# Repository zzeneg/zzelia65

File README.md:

# zzelia65

65% keyboard with external ProMicro-compatible controller.

Design inspired by [Neo Zelia](https://geekhack.org/index.php?topic=62449.0)

**⚠️ Design-stage only, not even a working prototype.**

## Main features

- Swappable controller, aimed to be wireless with [nice!nano](https://nicekeyboards.com/nice-nano/)
- Portable
- No plate
- No RGB
- Soldered switches

## Project structure

- `keyboard-layout.json` Layout file that can be imported into [keyboard-layout-editor](http://www.keyboard-layout-editor.com)
- `matrix-layout.json` Wiring configuration to be imported into [Keyboard Firmware Builder](https://builder.mrkeebs.com)
- `kicad` - KiCad project
- `gerber` - gerber files

## Layout

Standard 65% ANSI with exploded design.

## Wiring

ProMicro has only 18 pins by default so wiring is a bit tricky as we need to stay in the limit. The most logical was to use 10 rows and 8 columns. Can be improved, probably.

## Similar/inspirational projects

- [Contra](https://github.com/ai03-2725/Contra)
- [KBIC65](https://github.com/b-karl/KBIC65)
- [horizon](https://github.com/skarrmann/horizon)

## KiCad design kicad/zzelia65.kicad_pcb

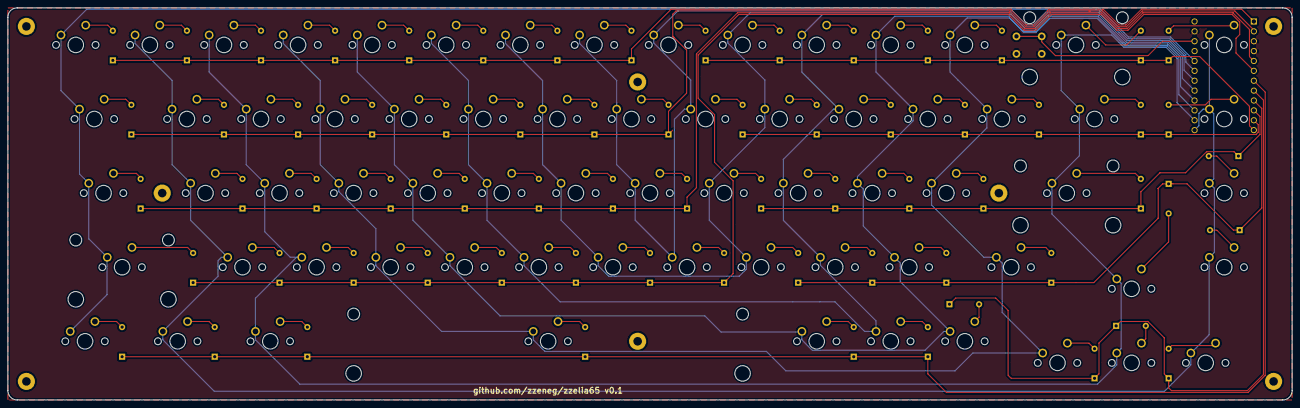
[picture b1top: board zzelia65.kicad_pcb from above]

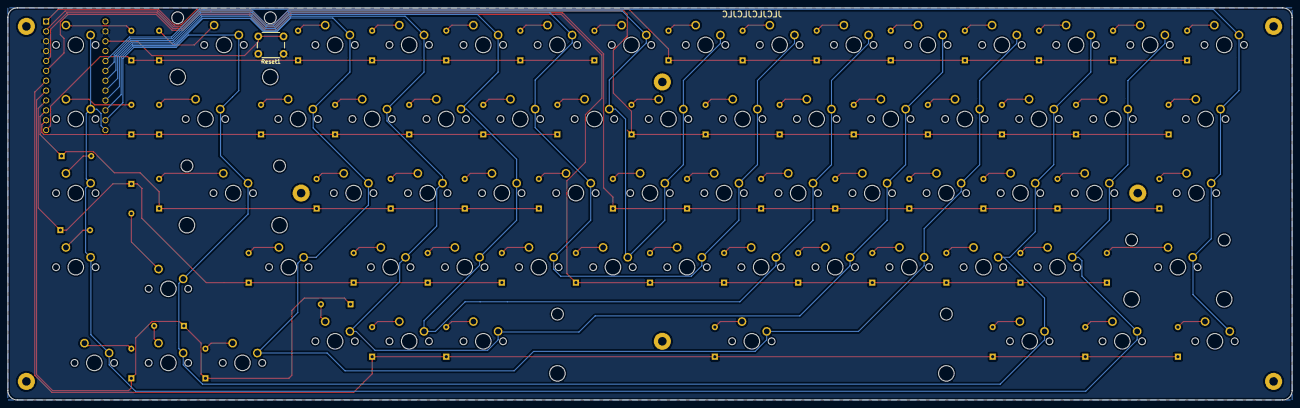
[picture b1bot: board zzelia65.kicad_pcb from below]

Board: 2 copper layers, 330.2 x 100.8 mm, 138 parts (2 on the bottom side), 10 nets.

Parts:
D_0, D_1, D_2, D_3, D_4, D_5, D_6, D_7, D_8, D_9: D_Small; D_DO-35_SOD27_P7.62mm_Horizontal
D_A1: D_Small; D_DO-35_SOD27_P7.62mm_Horizontal
D_B1: D_Small; D_DO-35_SOD27_P7.62mm_Horizontal
D_Back1: D_Small; D_DO-35_SOD27_P7.62mm_Horizontal
D_Backslash1: D_Small; D_DO-35_SOD27_P7.62mm_Horizontal
D_C1: D_Small; D_DO-35_SOD27_P7.62mm_Horizontal
D_Caps1: D_Small; D_DO-35_SOD27_P7.62mm_Horizontal
D_Close1: D_Small; D_DO-35_SOD27_P7.62mm_Horizontal
D_Comma1: D_Small; D_DO-35_SOD27_P7.62mm_Horizontal
D_D1: D_Small; D_DO-35_SOD27_P7.62mm_Horizontal
D_Del1: D_Small; D_DO-35_SOD27_P7.62mm_Horizontal
D_Dot1: D_Small; D_DO-35_SOD27_P7.62mm_Horizontal
D_Down1: D_Small; D_DO-35_SOD27_P7.62mm_Horizontal
D_E1: D_Small; D_DO-35_SOD27_P7.62mm_Horizontal
D_End1: D_Small; D_DO-35_SOD27_P7.62mm_Horizontal
D_Enter1: D_Small; D_DO-35_SOD27_P7.62mm_Horizontal
D_Esc1: D_Small; D_DO-35_SOD27_P7.62mm_Horizontal
D_F1: D_Small; D_DO-35_SOD27_P7.62mm_Horizontal
D_Fn1: D_Small; D_DO-35_SOD27_P7.62mm_Horizontal
D_G1: D_Small; D_DO-35_SOD27_P7.62mm_Horizontal
D_H1: D_Small; D_DO-35_SOD27_P7.62mm_Horizontal
D_Home1: D_Small; D_DO-35_SOD27_P7.62mm_Horizontal
D_I1: D_Small; D_DO-35_SOD27_P7.62mm_Horizontal
D_Insert1: D_Small; D_DO-35_SOD27_P7.62mm_Horizontal
D_J1: D_Small; D_DO-35_SOD27_P7.62mm_Horizontal
D_K1: D_Small; D_DO-35_SOD27_P7.62mm_Horizontal
D_L1: D_Small; D_DO-35_SOD27_P7.62mm_Horizontal
D_LAlt1: D_Small; D_DO-35_SOD27_P7.62mm_Horizontal
D_LCtrl1: D_Small; D_DO-35_SOD27_P7.62mm_Horizontal
D_LShift1: D_Small; D_DO-35_SOD27_P7.62mm_Horizontal
D_LWin1: D_Small; D_DO-35_SOD27_P7.62mm_Horizontal
D_Left1: D_Small; D_DO-35_SOD27_P7.62mm_Horizontal
D_M1: D_Small; D_DO-35_SOD27_P7.62mm_Horizontal
D_Minus1: D_Small; D_DO-35_SOD27_P7.62mm_Horizontal
D_N1: D_Small; D_DO-35_SOD27_P7.62mm_Horizontal
D_O1: D_Small; D_DO-35_SOD27_P7.62mm_Horizontal
D_Open1: D_Small; D_DO-35_SOD27_P7.62mm_Horizontal
D_P1: D_Small; D_DO-35_SOD27_P7.62mm_Horizontal
D_Plus1: D_Small; D_DO-35_SOD27_P7.62mm_Horizontal
D_Q1: D_Small; D_DO-35_SOD27_P7.62mm_Horizontal
D_Quote1: D_Small; D_DO-35_SOD27_P7.62mm_Horizontal
D_R1: D_Small; D_DO-35_SOD27_P7.62mm_Horizontal
D_RAlt1: D_Small; D_DO-35_SOD27_P7.62mm_Horizontal
D_RCtrl1: D_Small; D_DO-35_SOD27_P7.62mm_Horizontal
D_RShift1: D_Small; D_DO-35_SOD27_P7.62mm_Horizontal
D_Right1: D_Small; D_DO-35_SOD27_P7.62mm_Horizontal
D_S1: D_Small; D_DO-35_SOD27_P7.62mm_Horizontal
D_Semi1: D_Small; D_DO-35_SOD27_P7.62mm_Horizontal
D_Slash1: D_Small; D_DO-35_SOD27_P7.62mm_Horizontal
D_Space1: D_Small; D_DO-35_SOD27_P7.62mm_Horizontal
D_T1: D_Small; D_DO-35_SOD27_P7.62mm_Horizontal
D_Tab1: D_Small; D_DO-35_SOD27_P7.62mm_Horizontal
D_U1: D_Small; D_DO-35_SOD27_P7.62mm_Horizontal
D_Up1: D_Small; D_DO-35_SOD27_P7.62mm_Horizontal
D_V1: D_Small; D_DO-35_SOD27_P7.62mm_Horizontal
D_W1: D_Small; D_DO-35_SOD27_P7.62mm_Horizontal
D_X1: D_Small; D_DO-35_SOD27_P7.62mm_Horizontal
D_Y1: D_Small; D_DO-35_SOD27_P7.62mm_Horizontal
D_Z1: D_Small; D_DO-35_SOD27_P7.62mm_Horizontal
K_0, K_1, K_2, K_3, K_4, K_5, K_6, K_7, K_8, K_9: MX-NoLED; MXOnly-1U-NoLED
K_A1: MX-NoLED; MXOnly-1U-NoLED
K_B1: MX-NoLED; MXOnly-1U-NoLED
K_Back1: MX-NoLED; MXOnly-2U-NoLED
K_Backslash1: MX-NoLED; MXOnly-1.5U-NoLED
K_C1: MX-NoLED; MXOnly-1U-NoLED
K_Caps1: MX-NoLED; MXOnly-1.75U-NoLED
K_Close1: MX-NoLED; MXOnly-1U-NoLED
K_Comma1: MX-NoLED; MXOnly-1U-NoLED
K_D1: MX-NoLED; MXOnly-1U-NoLED
K_Del1: MX-NoLED; MXOnly-1U-NoLED
K_Dot1: MX-NoLED; MXOnly-1U-NoLED
K_Down1: MX-NoLED; MXOnly-1U-NoLED
K_E1: MX-NoLED; MXOnly-1U-NoLED
K_End1: MX-NoLED; MXOnly-1U-NoLED
K_Enter1: MX-NoLED; MXOnly-2.25U-NoLED
K_Esc1: MX-NoLED; MXOnly-1U-NoLED
K_F1: MX-NoLED; MXOnly-1U-NoLED
K_Fn1: MX-NoLED; MXOnly-1U-NoLED
K_G1: MX-NoLED; MXOnly-1U-NoLED
K_H1: MX-NoLED; MXOnly-1U-NoLED
K_Home1: MX-NoLED; MXOnly-1U-NoLED
K_I1: MX-NoLED; MXOnly-1U-NoLED
K_Insert1: MX-NoLED; MXOnly-1U-NoLED
K_J1: MX-NoLED; MXOnly-1U-NoLED
K_K1: MX-NoLED; MXOnly-1U-NoLED
K_L1: MX-NoLED; MXOnly-1U-NoLED
K_LAlt1: MX-NoLED; MXOnly-1.25U-NoLED
K_LCtrl1: MX-NoLED; MXOnly-1.25U-NoLED
K_LShift1: MX-NoLED; MXOnly-2.25U-NoLED
K_LWin1: MX-NoLED; MXOnly-1.25U-NoLED
K_Left1: MX-NoLED; MXOnly-1U-NoLED
K_M1: MX-NoLED; MXOnly-1U-NoLED
K_Minus1: MX-NoLED; MXOnly-1U-NoLED
K_N1: MX-NoLED; MXOnly-1U-NoLED
K_O1: MX-NoLED; MXOnly-1U-NoLED
K_Open1: MX-NoLED; MXOnly-1U-NoLED
K_P1: MX-NoLED; MXOnly-1U-NoLED
K_Plus1: MX-NoLED; MXOnly-1U-NoLED
K_Q1: MX-NoLED; MXOnly-1U-NoLED
K_Quote1: MX-NoLED; MXOnly-1U-NoLED
K_R1: MX-NoLED; MXOnly-1U-NoLED
K_RAlt1: MX-NoLED; MXOnly-1U-NoLED
K_RCtrl1: MX-NoLED; MXOnly-1U-NoLED
K_RShift1: MX-NoLED; MXOnly-1.75U-NoLED
K_Right1: MX-NoLED; MXOnly-1U-NoLED
K_S1: MX-NoLED; MXOnly-1U-NoLED
K_Semi1: MX-NoLED; MXOnly-1U-NoLED
K_Slash1: MX-NoLED; MXOnly-1U-NoLED
K_Space1: MX-NoLED; MXOnly-6.25U-NoLED
K_T1: MX-NoLED; MXOnly-1U-NoLED
K_Tab1: MX-NoLED; MXOnly-1.5U-NoLED
K_U1: MX-NoLED; MXOnly-1U-NoLED
K_Up1: MX-NoLED; MXOnly-1U-NoLED
K_V1: MX-NoLED; MXOnly-1U-NoLED
K_W1: MX-NoLED; MXOnly-1U-NoLED
K_X1: MX-NoLED; MXOnly-1U-NoLED
K_Y1: MX-NoLED; MXOnly-1U-NoLED
K_Z1: MX-NoLED; MXOnly-1U-NoLED
ProMicro1: ProMicro
Reset1: RESET; SW_PUSH_6mm

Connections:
Col_0: K_Caps1.1, K_Esc1.1, K_LCtrl1.1, K_LShift1.1, K_Tab1.1, ProMicro1.20
Col_1: K_1.1, K_A1.1, K_Del1.1, K_End1.1, K_Home1.1, K_Insert1.1, K_LWin1.1, K_Q1.1, K_Right1.1, K_Z1.1, ProMicro1.13
Col_2: K_2.1, K_Back1.1, K_Backslash1.1, K_Down1.1, K_Enter1.1, K_LAlt1.1, K_S1.1, K_Up1.1, K_W1.1, K_X1.1, ProMicro1.14
Col_3: K_3.1, K_C1.1, K_Close1.1, K_D1.1, K_E1.1, K_Left1.1, K_Plus1.1, K_Quote1.1, K_RShift1.1, K_Space1.1, ProMicro1.15
Col_4: K_4.1, K_F1.1, K_Minus1.1, K_Open1.1, K_R1.1, K_RAlt1.1, K_RCtrl1.1, K_Semi1.1, K_Slash1.1, K_V1.1, ProMicro1.16
Col_5: K_0.1, K_5.1, K_B1.1, K_Dot1.1, K_Fn1.1, K_G1.1, K_L1.1, K_P1.1, K_T1.1, ProMicro1.17
Col_6: K_6.1, K_9.1, K_Comma1.1, K_H1.1, K_K1.1, K_N1.1, K_O1.1, K_Y1.1, ProMicro1.18
Col_7: K_7.1, K_8.1, K_I1.1, K_J1.1, K_M1.1, K_U1.1, ProMicro1.19
GND: ProMicro1.3, ProMicro1.4, ProMicro1.23, Reset1.1
RESET: ProMicro1.22, Reset1.2

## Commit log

2021-11-30 initial pcb
2021-12-01 add jsons
2021-12-01 diodes
2021-12-01 edges & holes
2021-12-01 promicro & reset btn
2021-12-01 pcb zones
2021-12-01 18-pin
2021-12-02 routing
2021-12-02 remove reset button
2021-12-02 gerbers
2021-12-02 update layout
2021-12-02 readme
2021-12-07 reset button
2021-12-07 custom components
2021-12-07 update gerber
2021-12-07 JLCPCB text
2021-12-24 fix firmware builder settings
2021-12-24 update references
2022-09-21 add firmware
2022-09-22 add cover
2024-04-15 add adapter
